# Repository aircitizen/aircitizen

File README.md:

# AirCitizen

## Air quality measured by citizens

This is the main repo of the [aircitizen](http://www.aircitizen.org) project. The aircitizen project is a citizen science project about air quality.

We develop air quality measurement stations at [Fablab Sorbonne](https://fablab.sorbonne-universite.fr/) in Paris, France and organize participatory workshops (construction of the stations, measurements in a particular neighborhood, data visualization and discussion, ...) with citizens.

## Development

The project is currently under active development. Feel free to contact us if you want to join !

## License

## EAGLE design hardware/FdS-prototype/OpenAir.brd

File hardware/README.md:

<!---just a comment --->

This is the hardware page of the [AirCitizen](http://www.aircitizen.org) project. 

#  Mobile station

We developped this station for the Cité des sciences et de l'industrie and the turfu workshops.

1. arduino mega board
2. battery
3. grove mega shield
4. grove GPS
5. grove temperature and humidity sensor (DHT22)
6. PM sensor Plantower PMS3003 (non grove) with 4-pin adaptor and grove cable
7. I2C OLED display
8. uSD card reader/writer (non grove) with 8Go SD card

The station can be assembled by connecting the various components to the shield using grove cable. The SD reader/writer is the exception. It uses the SPI protocol to communicate with the MEGA and must be connected to the Arduino using jumper cables.

# Fixed station (requires power supply and wifi)

We adapted the [Luftdaten](https://luftdaten.info/) to include a noise sensor for a deployment in the north of Paris. 

## Bill of Materials
### fixed station rev 1

Component Refs | Type            | Value      | Package | Qty | Supplier #
-------------- | --------------- | ---------- | ------- | :-: | ------------
MCU            | NodeMCU         | -          | -    |  1  | [Amazon](https://www.amazon.fr/ESP8266-nodeMCU/s?k=ESP8266+nodeMCU)
SDS011         | SDS011 dust sensor | -       | -    |  1  | -

</br></br>

To be completed.

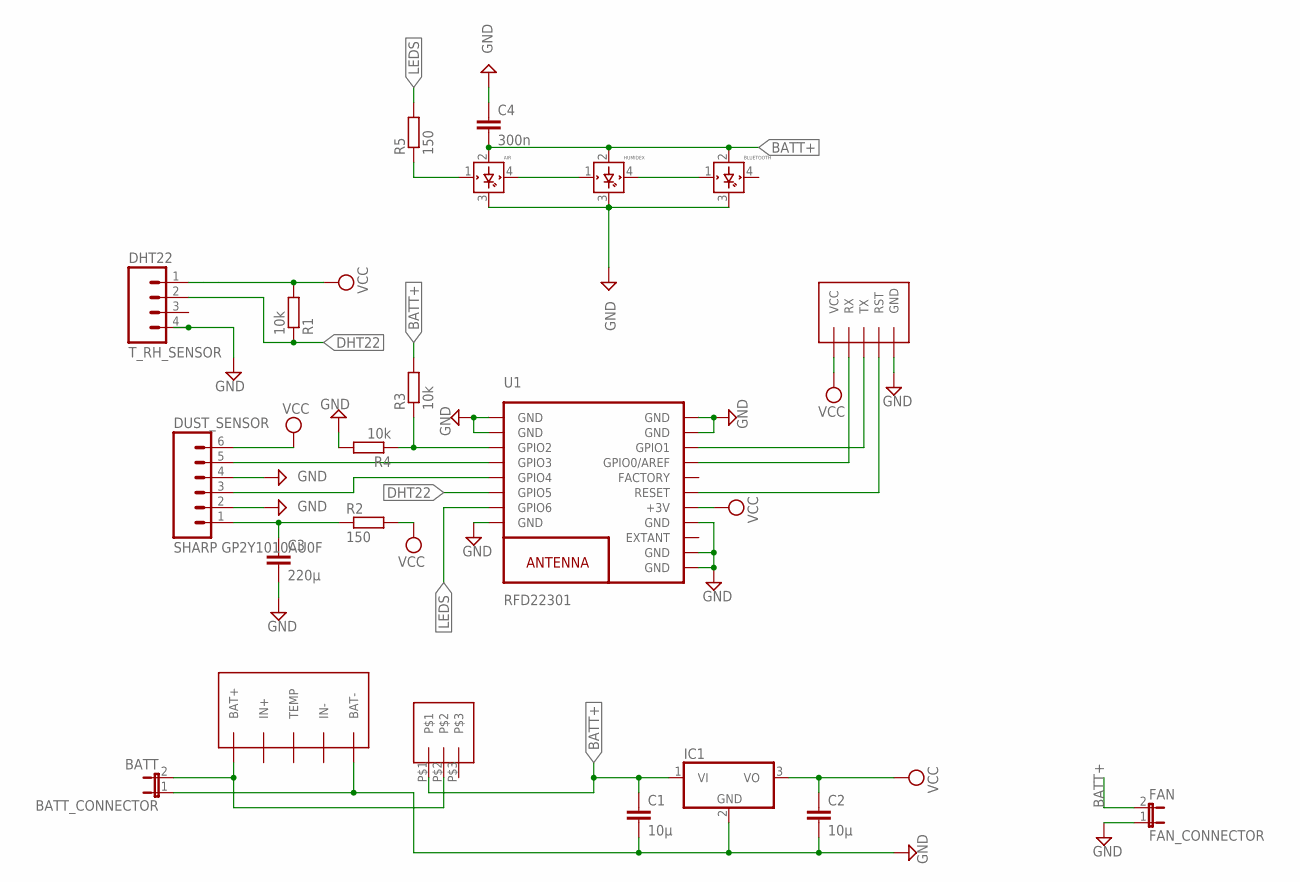
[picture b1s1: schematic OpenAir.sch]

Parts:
AIR: WS2812BRGB; LED5MMRGB
BATT_CONNECTOR: BATT; JP1
BLUETOOTH: WS2812BRGB; LED5MMRGB
C1, C2: 10µ; C025-030X050
C3: 220µ; C025-030X050
C4: 300n; C025-030X050
DUST_SENSOR: SHARP GP2Y1010AU0F; 1X06_LONGPADS
FAN_CONNECTOR: FAN; JP1
HUMIDEX: WS2812BRGB; LED5MMRGB
IC1: 78T; TO220H
R1, R3, R4: 10k; 0207/10
R2, R5: 150; 0207/10
T_RH_SENSOR: DHT22; JST-4-PTH-VERT
U1: RFD22301
U$1: IC_PROG
U$4: BATT_CHARG
U$5: SPSTCUSTOM

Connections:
BATT+: AIR.2 (VDD), BLUETOOTH.2 (VDD), C1.1, C4.2, FAN_CONNECTOR.2, HUMIDEX.2 (VDD), IC1.1 (VI), R3.2, U$5.P$1
DHT22: R1.1, T_RH_SENSOR.2, U1.6 (GPIO5)
GND: AIR.3 (GND), BATT_CONNECTOR.1, BLUETOOTH.3 (GND), C1.2, C2.2, C3.2, C4.1, DUST_SENSOR.2, DUST_SENSOR.4, FAN_CONNECTOR.1, HUMIDEX.3 (GND), IC1.2 (GND), R4.2, T_RH_SENSOR.4, U1.1 (GND), U1.2 (GND), U1.8 (GND), U1.9 (GND), U1.10 (GND), U1.12 (GND), U1.18 (GND), U1.19 (GND), U$1.GND, U$4.BAT-
LEDS: R5.2, U1.7 (GPIO6)
unnamed: AIR.4 (DOUT), HUMIDEX.1 (DIN)
unnamed: U1.14 (RESET), U$1.RST
unnamed: BLUETOOTH.1 (DIN), HUMIDEX.4 (DOUT)
unnamed: U1.16 (GPIO0/AREF), U$1.RX
unnamed: U1.17 (GPIO1), U$1.TX
unnamed: DUST_SENSOR.5, U1.4 (GPIO3)
unnamed: DUST_SENSOR.3, U1.5 (GPIO4)
unnamed: C3.1, DUST_SENSOR.1, R2.1
unnamed: R3.1, R4.1, U1.3 (GPIO2)
unnamed: BATT_CONNECTOR.2, U$4.BAT+, U$5.P$2
unnamed: AIR.1 (DIN), R5.1
VCC: C2.1, DUST_SENSOR.6, IC1.3 (VO), R1.2, R2.2, T_RH_SENSOR.1, U1.13 (+3V), U$1.VCC

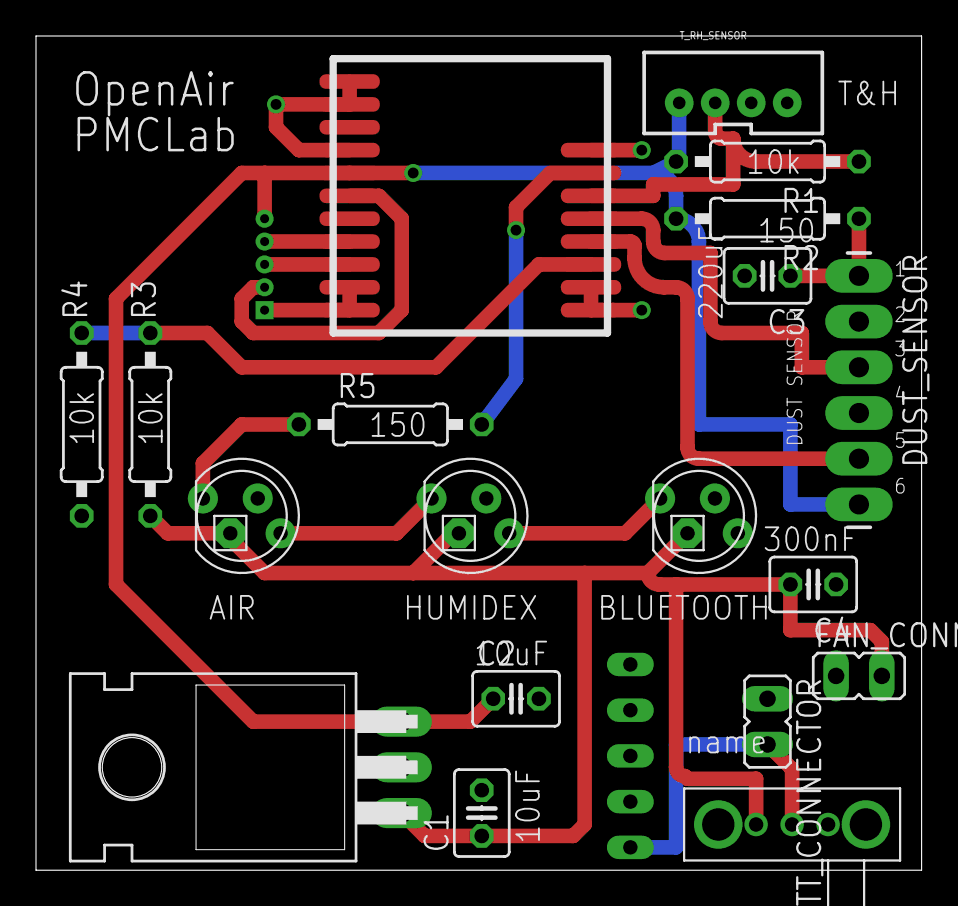
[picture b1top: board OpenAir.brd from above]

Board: 2 copper layers, 49.2 x 46.3 mm, 21 parts (0 on the bottom side), 16 nets.

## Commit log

2018-07-21 change in readme
2018-07-21 change tree structure
2018-07-21 add svg
2018-07-21 added Eagle files
2018-07-21 changed readme
2018-07-23 added CN2 firmware
2018-10-01 Add turfu station libs and firmwares
2018-10-11 Add READMEs
2018-10-14 Add photo CN2 station
2018-10-14 Change READMEs
2018-10-14 Add turfu prototype
2019-02-09 test
2019-04-07 add ecocity2030
2019-04-07 ecocity2030
2019-04-17 boitier_v3
    plan pour un boitier fabriqué par impression 3D (dépôt de fil, PLA)
2019-05-16 add masterclass software
2019-05-25 plans et photos
    Nouveau concept de "boitier" pour la version avec carte Lotus, fonctionne aussi avec un Arduino MEGA + shield grove en occupant l'emplacement vide qui peut servir à ranger les cables.
2019-09-16 update hardware
2019-10-20 fix wrong link
2020-01-15 add DANE workshop files
2023-09-25 fix bad links

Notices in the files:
README.md:
License:
[License: CC BY-NC 4.0](http://creativecommons.org/licenses/by-nc/4.0/)
parts and their libraries:
SparkFun-Connectors: Licensing: Creative Commons ShareAlike 4.0 International - https://creativecommons.org/licenses/by-sa/4.0
